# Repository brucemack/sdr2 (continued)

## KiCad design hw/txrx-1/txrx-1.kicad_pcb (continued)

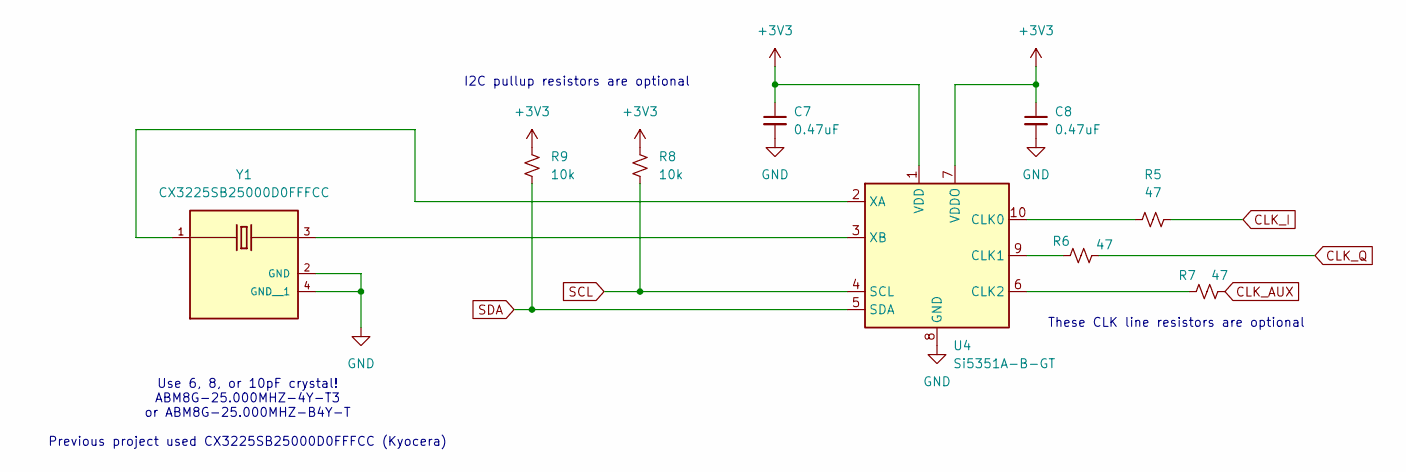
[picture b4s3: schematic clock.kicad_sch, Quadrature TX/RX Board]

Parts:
C7, C8: 0.47uF; C_0805_2012Metric_Pad1.18x1.45mm_HandSolder
R5, R6, R7: 47; R_0805_2012Metric_Pad1.20x1.40mm_HandSolder
R8, R9: 10k; R_0805_2012Metric_Pad1.20x1.40mm_HandSolder
U4: Si5351A-B-GT; MSOP-10_3x3mm_P0.5mm
Y1: CX3225SB25000D0FFFCC; OSCCC320X250X60N; PARTREV N/A

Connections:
+3V3: C7.1, C8.1, R8.1, R9.1, U4.1 (VDD), U4.7 (VDDO); also elsewhere on the board
CLK_AUX: R7.2; also elsewhere on the board
CLK_I: R5.2; also elsewhere on the board
CLK_Q: R6.2; also elsewhere on the board
GND: C7.2, C8.2, U4.8 (GND), Y1.2 (GND), Y1.4 (GND__1); also elsewhere on the board
unnamed: R5.1, U4.10 (CLK0)
unnamed: R6.1, U4.9 (CLK1)
unnamed: R7.1, U4.6 (CLK2)
unnamed: U4.2 (XA), Y1.1
unnamed: U4.3 (XB), Y1.3
SCL: R8.2, U4.4 (SCL); also elsewhere on the board
SDA: R9.2, U4.5 (SDA); also elsewhere on the board

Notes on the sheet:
These CLK line resistors are optional
I2C pullup resistors are optional
Use 6, 8, or 10pF crystal! ABM8G-25.000MHZ-4Y-T3 or ABM8G-25.000MHZ-B4Y-T Previous project used CX3225SB25000D0FFFCC (Kyocera)

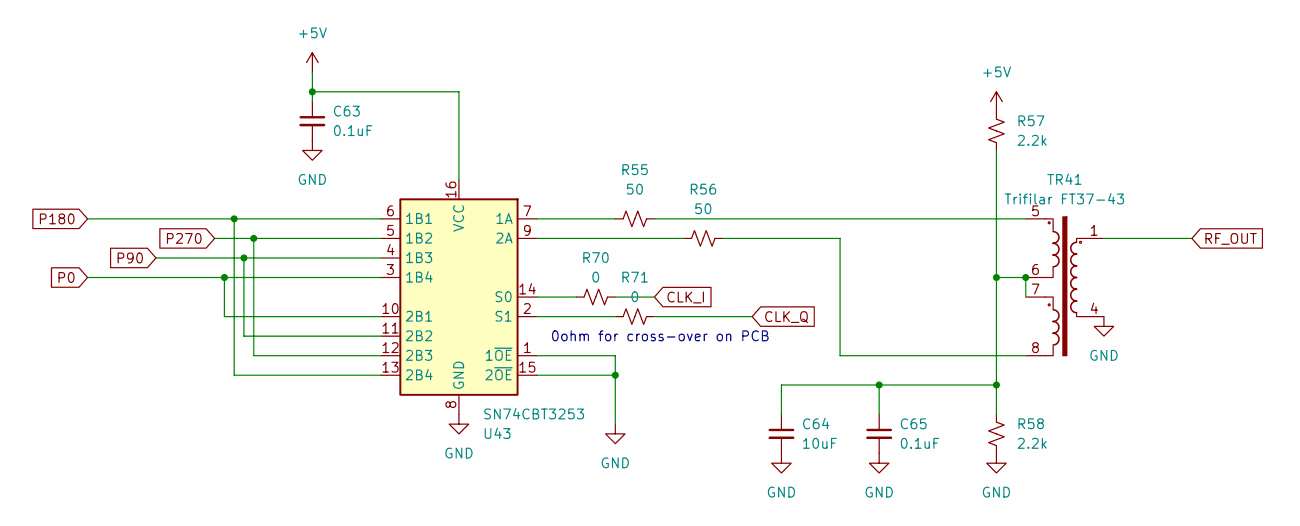
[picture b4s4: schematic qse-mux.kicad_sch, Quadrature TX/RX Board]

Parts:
C63, C65: 0.1uF; C_0805_2012Metric_Pad1.18x1.45mm_HandSolder
C64: 10uF; C_0805_2012Metric_Pad1.18x1.45mm_HandSolder
R55, R56: 50; R_0805_2012Metric_Pad1.20x1.40mm_HandSolder
R57, R58: 2.2k; R_0805_2012Metric_Pad1.20x1.40mm_HandSolder
R70, R71: 0; R_0805_2012Metric_Pad1.20x1.40mm_HandSolder
TR41: Trifilar FT37-43; FT37-43 Trifilar
U43: SN74CBT3253; SOIC-16_3.9x9.9mm_P1.27mm

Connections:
+5V: C63.1, R57.1, U43.16 (VCC); also elsewhere on the board
CLK_I: R70.2; also elsewhere on the board
CLK_Q: R71.2; also elsewhere on the board
GND: C63.2, C64.2, C65.2, R58.2, TR41.4, U43.1 (1~OE), U43.8 (GND), U43.15 (2~OE); also elsewhere on the board
unnamed: C64.1, C65.1, R57.2, R58.1, TR41.6, TR41.7
unnamed: R55.2, TR41.5
unnamed: R56.2, TR41.8
unnamed: R55.1, U43.7 (1A)
unnamed: R56.1, U43.9 (2A)
unnamed: R70.1, U43.14 (S0)
unnamed: R71.1, U43.2 (S1)
P0: U43.3 (1B4), U43.10 (2B1); also elsewhere on the board
P90: U43.4 (1B3), U43.11 (2B2); also elsewhere on the board
P180: U43.6 (1B1), U43.13 (2B4); also elsewhere on the board
P270: U43.5 (1B2), U43.12 (2B3); also elsewhere on the board
RF_OUT: TR41.1; also elsewhere on the board

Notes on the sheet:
0ohm for cross-over on PCB

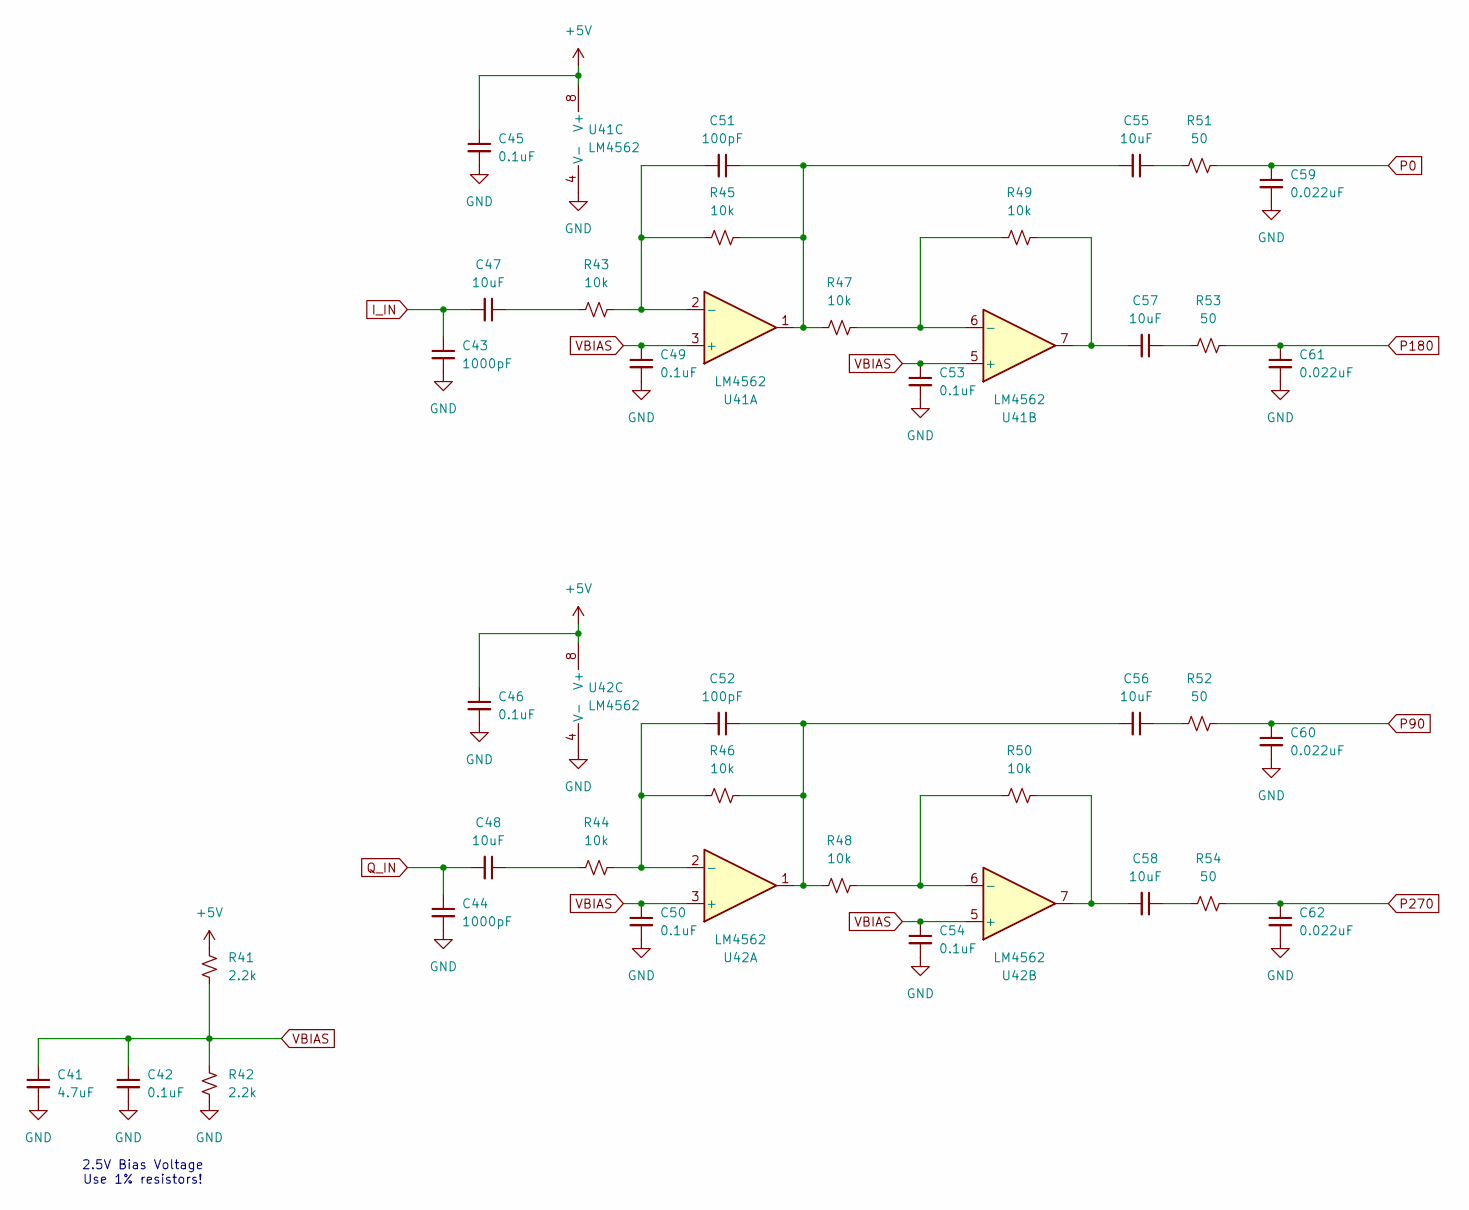
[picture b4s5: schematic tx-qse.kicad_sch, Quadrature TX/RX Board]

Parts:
C41: 4.7uF; C_0805_2012Metric_Pad1.18x1.45mm_HandSolder
C42, C45, C46, C49, C50, C53, C54: 0.1uF; C_0805_2012Metric_Pad1.18x1.45mm_HandSolder
C43, C44: 1000pF; C_0805_2012Metric_Pad1.18x1.45mm_HandSolder
C47, C48, C55, C56, C57, C58: 10uF; C_0805_2012Metric_Pad1.18x1.45mm_HandSolder
C51, C52: 100pF; C_0805_2012Metric_Pad1.18x1.45mm_HandSolder
C59, C60, C61, C62: 0.022uF; C_0805_2012Metric_Pad1.18x1.45mm_HandSolder
R41, R42: 2.2k; R_0805_2012Metric_Pad1.20x1.40mm_HandSolder
R43, R44, R45, R46, R47, R48, R49, R50: 10k; R_0805_2012Metric_Pad1.20x1.40mm_HandSolder
R51, R52, R53, R54: 50; R_0805_2012Metric_Pad1.20x1.40mm_HandSolder
U41, U42: LM4562; SOIC-8_3.9x4.9mm_P1.27mm

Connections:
+5V: C45.1, C46.1, R41.1, U41.8 (V+), U42.8 (V+); also elsewhere on the board
GND: C41.2, C42.2, C43.2, C44.2, C45.2, C46.2, C49.2, C50.2, C53.2, C54.2, C59.2, C60.2, C61.2, C62.2, R42.2, U41.4 (V-), U42.4 (V-); also elsewhere on the board
I_IN: C43.1, C47.2; also elsewhere on the board
unnamed: C47.1, R43.1
unnamed: C48.1, R44.1
unnamed: C51.1, C55.2, R45.2, R47.1, U41.1
unnamed: C52.1, C56.2, R46.2, R48.1, U42.1
unnamed: C55.1, R51.1
unnamed: C56.1, R52.1
unnamed: C57.1, R53.1
unnamed: C57.2, R49.2, U41.7
unnamed: C58.1, R54.1
unnamed: C58.2, R50.2, U42.7
unnamed: C51.2, R43.2, R45.1, U41.2 (-)
unnamed: R47.2, R49.1, U41.6 (-)
unnamed: C52.2, R44.2, R46.1, U42.2 (-)
unnamed: R48.2, R50.1, U42.6 (-)
P0: C59.1, R51.2; also elsewhere on the board
P90: C60.1, R52.2; also elsewhere on the board
P180: C61.1, R53.2; also elsewhere on the board
P270: C62.1, R54.2; also elsewhere on the board
Q_IN: C44.1, C48.2; also elsewhere on the board
VBIAS: C41.1, C42.1, C49.1, C50.1, C53.1, C54.1, R41.2, R42.1, U41.3 (+), U41.5 (+), U42.3 (+), U42.5 (+)

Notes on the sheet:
2.5V Bias Voltage Use 1% resistors!

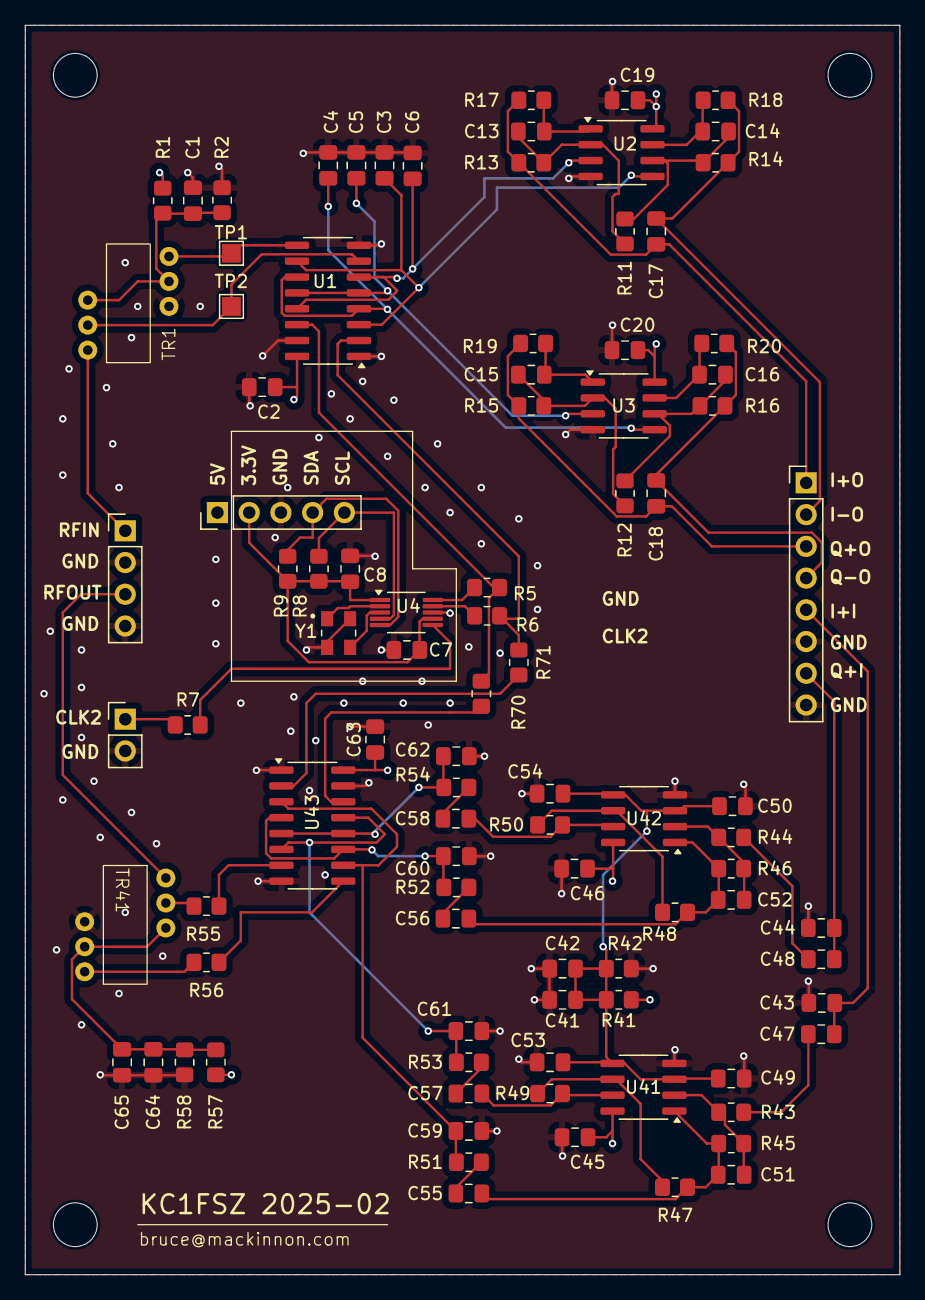
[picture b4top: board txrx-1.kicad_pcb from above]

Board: 4 copper layers, 70.0 x 100.0 mm, 98 parts (0 on the bottom side), 62 nets.

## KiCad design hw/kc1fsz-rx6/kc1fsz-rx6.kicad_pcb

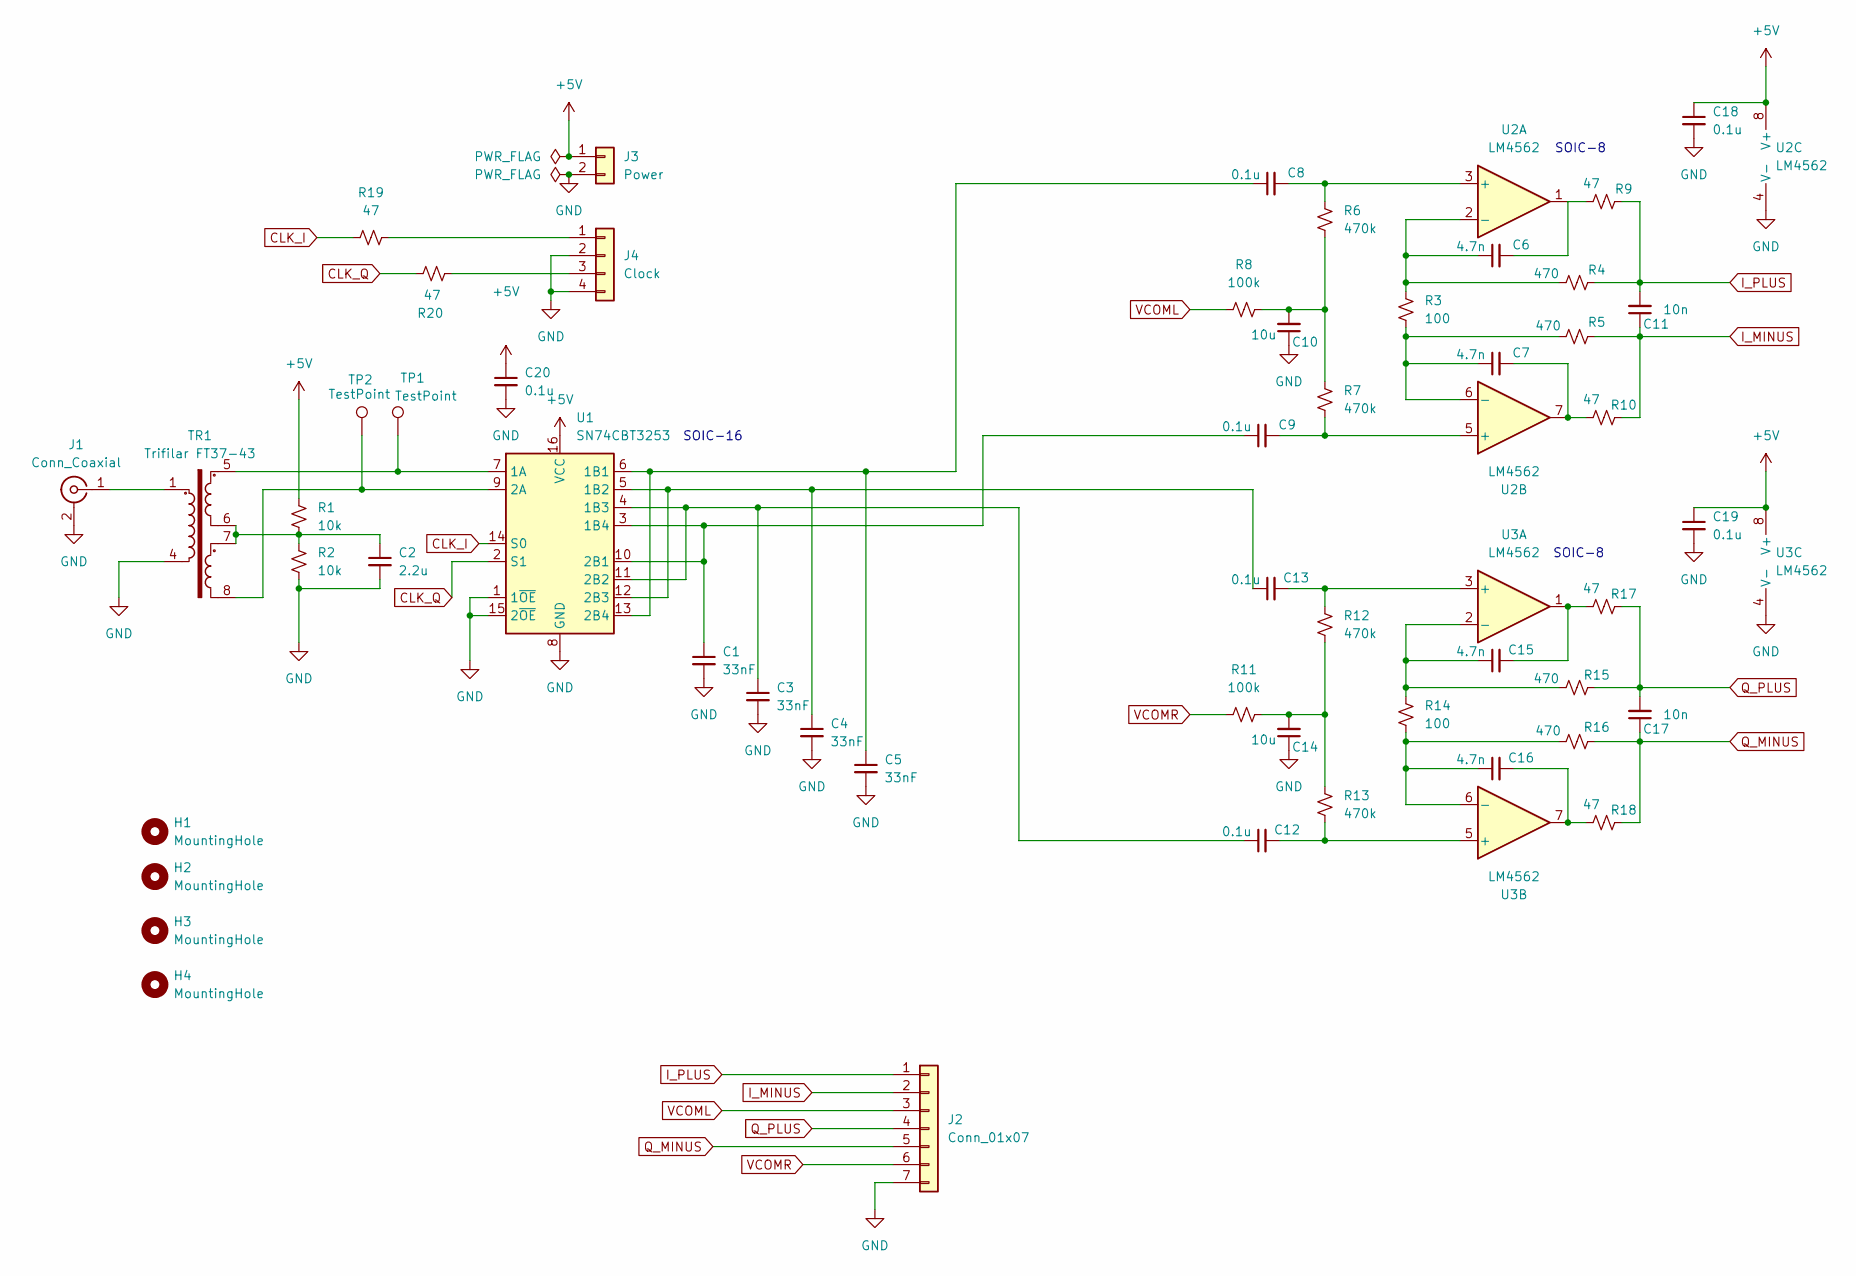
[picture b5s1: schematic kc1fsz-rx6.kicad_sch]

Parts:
C1, C3, C4, C5: 33nF; C_0805_2012Metric_Pad1.18x1.45mm_HandSolder
C2: 2.2u; C_0805_2012Metric_Pad1.18x1.45mm_HandSolder
C6, C7, C15, C16: 4.7n; C_0805_2012Metric_Pad1.18x1.45mm_HandSolder
C8, C9, C12, C13, C18, C19, C20: 0.1u; C_0805_2012Metric_Pad1.18x1.45mm_HandSolder
C10, C14: 10u; C_0805_2012Metric_Pad1.18x1.45mm_HandSolder
C11, C17: 10n; C_0805_2012Metric_Pad1.18x1.45mm_HandSolder
H1, H2, H3, H4: MountingHole; MountingHole_3.5mm
J1: Conn_Coaxial; SMA_Amphenol_901-144_Vertical
J2: Conn_01x07; PinHeader_1x07_P2.54mm_Vertical
J3: Power; PinHeader_1x02_P2.54mm_Vertical
J4: Clock; PinHeader_1x04_P2.54mm_Vertical
R1, R2: 10k; R_0805_2012Metric_Pad1.20x1.40mm_HandSolder
R3, R14: 100; R_0805_2012Metric_Pad1.20x1.40mm_HandSolder
R4, R5, R15, R16: 470; R_0805_2012Metric_Pad1.20x1.40mm_HandSolder
R6, R7, R12, R13: 470k; R_0805_2012Metric_Pad1.20x1.40mm_HandSolder
R8, R11: 100k; R_0805_2012Metric_Pad1.20x1.40mm_HandSolder
R9, R10, R17, R18, R19, R20: 47; R_0805_2012Metric_Pad1.20x1.40mm_HandSolder
TP1, TP2: TestPoint; TestPoint_Pad_1.5x1.5mm
TR1: Trifilar FT37-43; FT37-43 Trifilar
U1: SN74CBT3253; SOIC-16_3.9x9.9mm_P1.27mm
U2, U3: LM4562; SOIC-8_3.9x4.9mm_P1.27mm

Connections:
+5V: C18.1, C19.1, C20.1, J3.1, R1.1, U1.16 (VCC), U2.8 (V+), U3.8 (V+)
CLK_I: R19.1, U1.14 (S0)
CLK_Q: R20.1, U1.2 (S1)
GND: C1.2, C2.2, C3.2, C4.2, C5.2, C10.1, C14.1, C18.2, C19.2, C20.2, J1.2 (Ext), J2.7, J3.2, J4.2, J4.4, R2.2, TR1.4, U1.1 (1~OE), U1.8 (GND), U1.15 (2~OE), U2.4 (V-), U3.4 (V-)
I_MINUS: C11.1, J2.2, R5.2, R10.2
I_PLUS: C11.2, J2.1, R4.2, R9.2
unnamed: C2.1, R1.2, R2.1, TR1.6, TR1.7
unnamed: C6.2, R9.1, U2.1
unnamed: C7.2, R10.1, U2.7
unnamed: C10.2, R6.2, R7.1, R8.2
unnamed: C14.2, R11.2, R12.2, R13.1
unnamed: C15.2, R17.1, U3.1
unnamed: C16.2, R18.1, U3.7
unnamed: J1.1 (In), TR1.1
unnamed: J4.1, R19.2
unnamed: J4.3, R20.2
unnamed: TP1.1, TR1.5, U1.7 (1A)
unnamed: C5.1, C8.1, U1.6 (1B1), U1.13 (2B4)
unnamed: C4.1, C13.1, U1.5 (1B2), U1.12 (2B3)
unnamed: C3.1, C12.1, U1.4 (1B3), U1.11 (2B2)
unnamed: C1.1, C9.1, U1.3 (1B4), U1.10 (2B1)
unnamed: TP2.1, TR1.8, U1.9 (2A)
unnamed: C8.2, R6.1, U2.3 (+)
unnamed: C6.1, R3.1, R4.1, U2.2 (-)
unnamed: C9.2, R7.2, U2.5 (+)
unnamed: C7.1, R3.2, R5.1, U2.6 (-)
unnamed: C13.2, R12.1, U3.3 (+)
unnamed: C15.1, R14.1, R15.1, U3.2 (-)
unnamed: C12.2, R13.2, U3.5 (+)
unnamed: C16.1, R14.2, R16.1, U3.6 (-)
Q_MINUS: C17.1, J2.5, R16.2, R18.2
Q_PLUS: C17.2, J2.4, R15.2, R17.2
VCOML: J2.3, R8.1
VCOMR: J2.6, R11.1

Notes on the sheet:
SOIC-8
SOIC-16

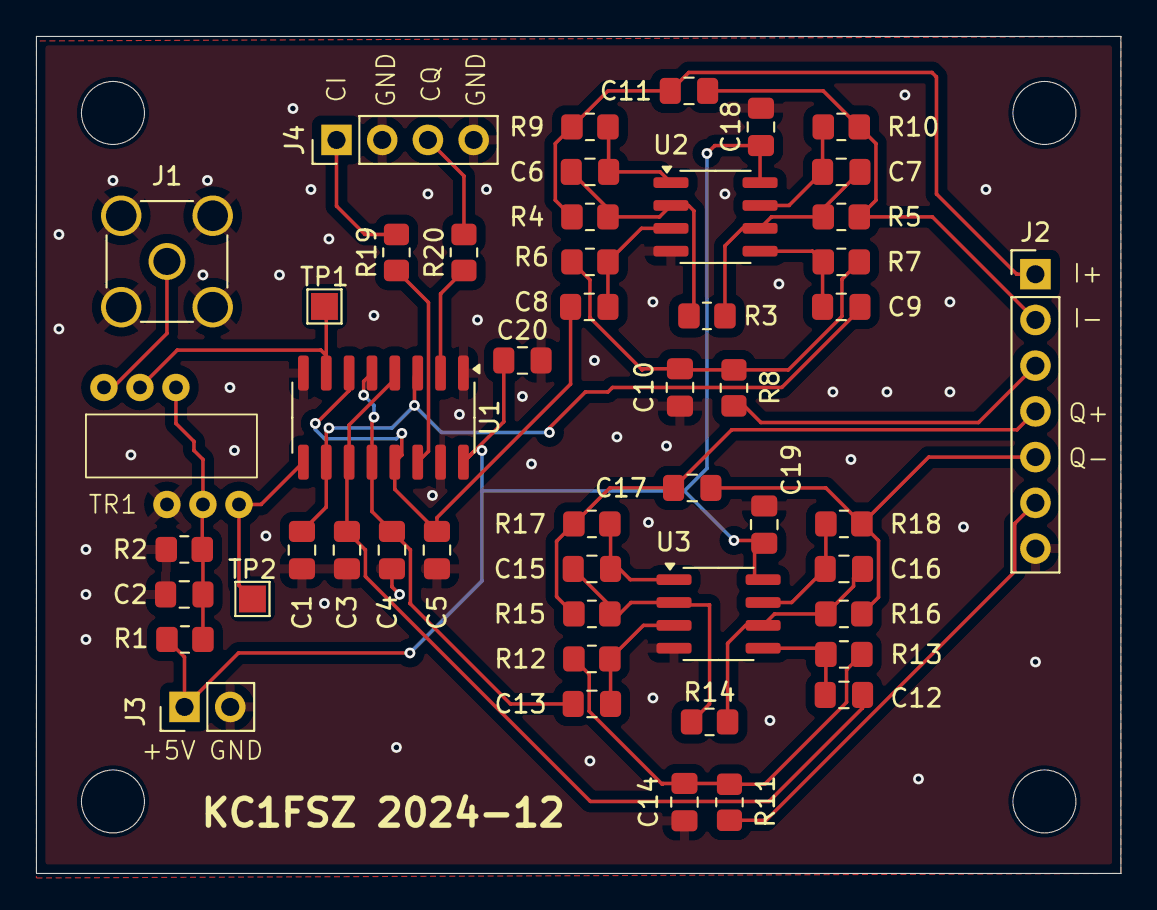
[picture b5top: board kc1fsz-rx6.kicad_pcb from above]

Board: 2 copper layers, 60.2 x 46.5 mm, 54 parts (0 on the bottom side), 34 nets.

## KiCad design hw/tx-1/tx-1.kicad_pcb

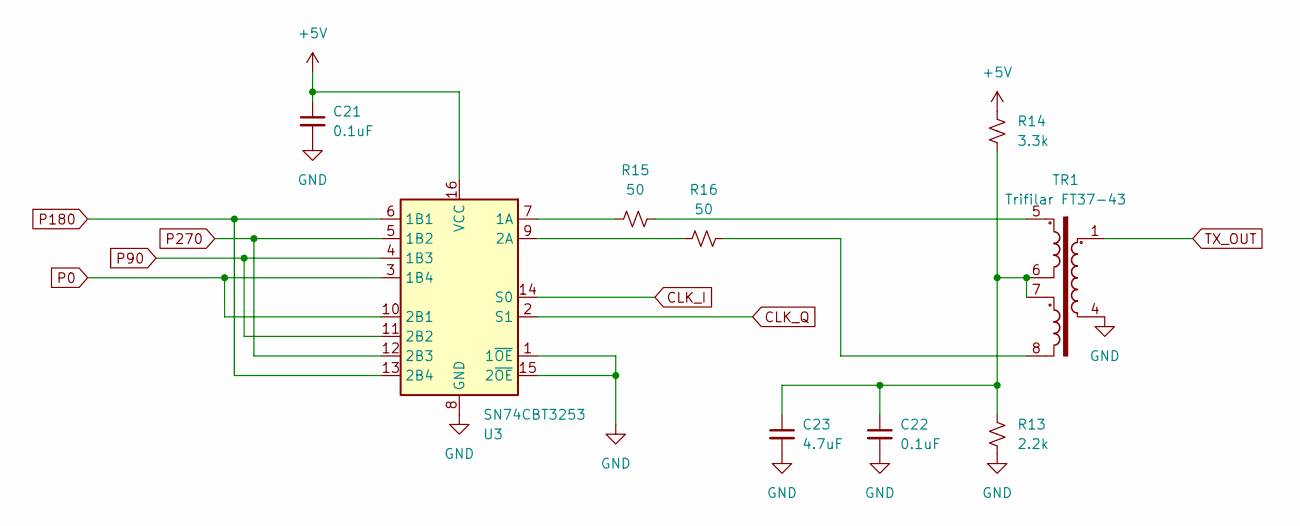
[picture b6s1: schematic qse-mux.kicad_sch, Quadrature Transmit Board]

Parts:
C21, C22: 0.1uF; C_0805_2012Metric_Pad1.18x1.45mm_HandSolder
C23: 4.7uF; C_0805_2012Metric_Pad1.18x1.45mm_HandSolder
R13: 2.2k; R_0805_2012Metric_Pad1.20x1.40mm_HandSolder
R14: 3.3k; R_0805_2012Metric_Pad1.20x1.40mm_HandSolder
R15, R16: 50; R_0805_2012Metric_Pad1.20x1.40mm_HandSolder
TR1: Trifilar FT37-43; FT37-43 Trifilar
U3: SN74CBT3253; SOIC-16_3.9x9.9mm_P1.27mm

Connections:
+5V: C21.1, R14.1, U3.16 (VCC); also elsewhere on the board
CLK_I: U3.14 (S0); also elsewhere on the board
CLK_Q: U3.2 (S1); also elsewhere on the board
GND: C21.2, C22.2, C23.2, R13.2, TR1.4, U3.1 (1~OE), U3.8 (GND), U3.15 (2~OE); also elsewhere on the board
unnamed: C22.1, C23.1, R13.1, R14.2, TR1.6, TR1.7
unnamed: R15.2, TR1.5
unnamed: R16.2, TR1.8
unnamed: R15.1, U3.7 (1A)
unnamed: R16.1, U3.9 (2A)
P0: U3.3 (1B4), U3.10 (2B1); also elsewhere on the board
P90: U3.4 (1B3), U3.11 (2B2); also elsewhere on the board
P180: U3.6 (1B1), U3.13 (2B4); also elsewhere on the board
P270: U3.5 (1B2), U3.12 (2B3); also elsewhere on the board
TX_OUT: TR1.1; also elsewhere on the board

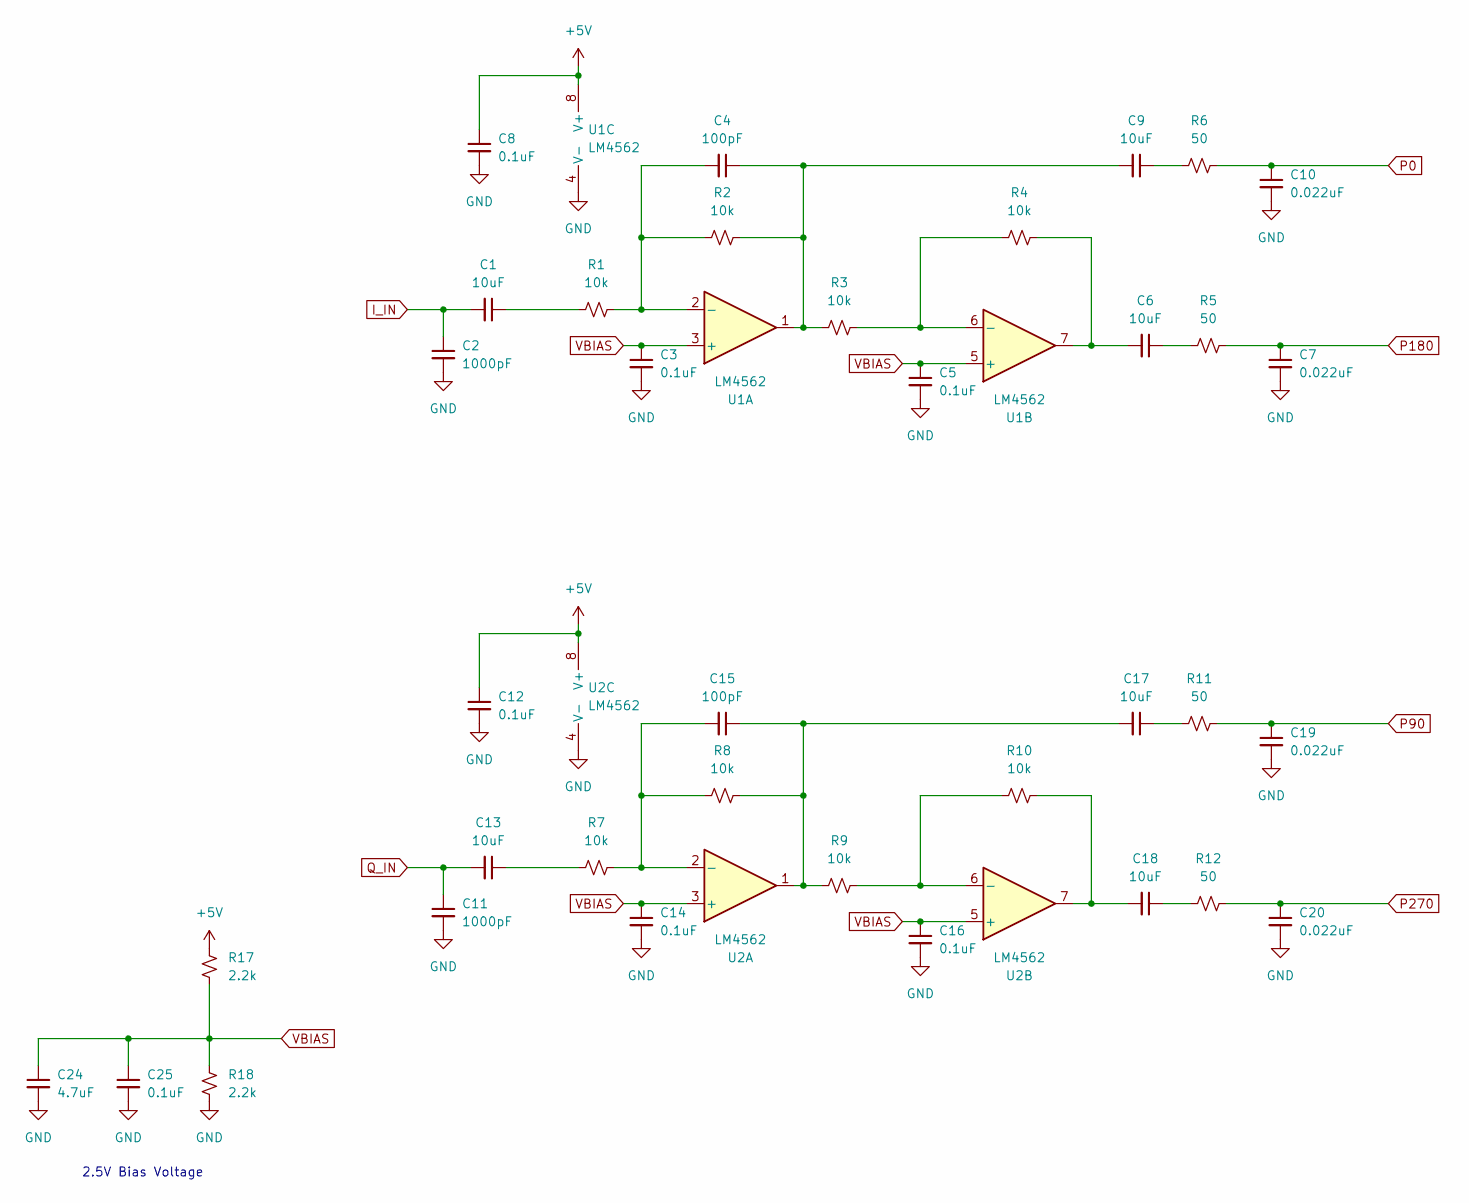
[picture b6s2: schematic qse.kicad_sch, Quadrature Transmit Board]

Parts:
C1, C6, C9, C13, C17, C18: 10uF; C_0805_2012Metric_Pad1.18x1.45mm_HandSolder
C2, C11: 1000pF; C_0805_2012Metric_Pad1.18x1.45mm_HandSolder
C3, C5, C8, C12, C14, C16, C25: 0.1uF; C_0805_2012Metric_Pad1.18x1.45mm_HandSolder
C4, C15: 100pF; C_0805_2012Metric_Pad1.18x1.45mm_HandSolder
C7, C10, C19, C20: 0.022uF; C_0805_2012Metric_Pad1.18x1.45mm_HandSolder
C24: 4.7uF; C_0805_2012Metric_Pad1.18x1.45mm_HandSolder
R1, R2, R3, R4, R7, R8, R9, R10: 10k; R_0805_2012Metric_Pad1.20x1.40mm_HandSolder
R5, R6, R11, R12: 50; R_0805_2012Metric_Pad1.20x1.40mm_HandSolder
R17, R18: 2.2k; R_0805_2012Metric_Pad1.20x1.40mm_HandSolder
U1, U2: LM4562; SOIC-8_3.9x4.9mm_P1.27mm

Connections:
+5V: C8.1, C12.1, R17.1, U1.8 (V+), U2.8 (V+); also elsewhere on the board
GND: C2.2, C3.2, C5.2, C7.2, C8.2, C10.2, C11.2, C12.2, C14.2, C16.2, C19.2, C20.2, C24.2, C25.2, R18.2, U1.4 (V-), U2.4 (V-); also elsewhere on the board
I_IN: C1.2, C2.1; also elsewhere on the board
unnamed: C1.1, R1.1
unnamed: C4.1, C9.2, R2.2, R3.1, U1.1
unnamed: C6.1, R5.1
unnamed: C6.2, R4.2, U1.7
unnamed: C9.1, R6.1
unnamed: C13.1, R7.1
unnamed: C15.1, C17.2, R8.2, R9.1, U2.1
unnamed: C17.1, R11.1
unnamed: C18.1, R12.1
unnamed: C18.2, R10.2, U2.7
unnamed: C4.2, R1.2, R2.1, U1.2 (-)
unnamed: R3.2, R4.1, U1.6 (-)
unnamed: C15.2, R7.2, R8.1, U2.2 (-)
unnamed: R9.2, R10.1, U2.6 (-)
P0: C10.1, R6.2; also elsewhere on the board
P90: C19.1, R11.2; also elsewhere on the board
P180: C7.1, R5.2; also elsewhere on the board
P270: C20.1, R12.2; also elsewhere on the board
Q_IN: C11.1, C13.2; also elsewhere on the board
VBIAS: C3.1, C5.1, C14.1, C16.1, C24.1, C25.1, R17.2, R18.1, U1.3 (+), U1.5 (+), U2.3 (+), U2.5 (+)

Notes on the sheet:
2.5V Bias Voltage

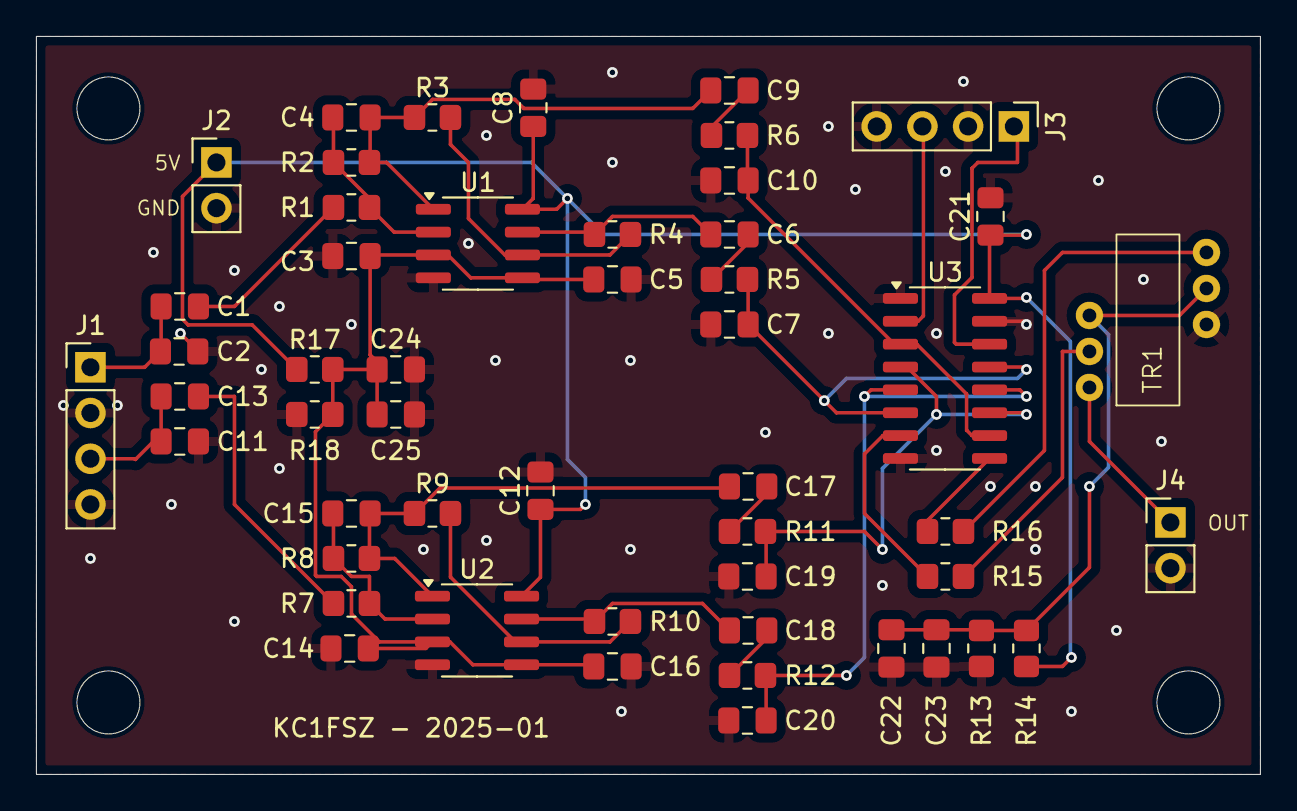
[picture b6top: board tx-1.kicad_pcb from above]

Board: 2 copper layers, 68.0 x 41.0 mm, 55 parts (0 on the bottom side), 31 nets.

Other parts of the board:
H1, H2, H3, H4: MountingHole; MountingHole_3.5mm
J1, J3: Conn_01x04; PinHeader_1x04_P2.54mm_Vertical
J2, J4: Conn_01x02; PinHeader_1x02_P2.54mm_Vertical

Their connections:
+5V: J2.1; also elsewhere on the board
CLK_I: J3.1; also elsewhere on the board
CLK_Q: J3.3; also elsewhere on the board
GND: J1.2, J1.4, J2.2, J3.2, J3.4, J4.2; also elsewhere on the board
I_IN: J1.1; also elsewhere on the board
Q_IN: J1.3; also elsewhere on the board
TX_OUT: J4.1; also elsewhere on the board

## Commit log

2025-01-20 SSB rejection seems to be working
2025-01-21 Working well
2025-01-24 Adding DAC
2025-01-24 First successful audio demo
2025-01-24 Added overflow detector
2025-01-25 Added sweep
2025-01-26 Working on tests
2025-01-26 Moving in hardware projects
2025-01-27 Ready to send audio breakout to fab
2025-01-28 TX board
2025-01-28 Working on TX
2025-01-29 Layout of TX board complete
2025-01-29 Ready to sent to fab
2025-02-04 Master generation of BCK and LRCK working
2025-02-05 Still debugging slave mode
2025-02-05 Slave mode problem resoled, now having a timing issue
2025-02-05 System working with PCM1804 in slave mode
2025-02-09 DAC working with DMA finally!
2025-02-10 Switched over to SMSIS DSP functions - not tested yet.
2025-02-11 Getting very close to working. Still a problem with pure tones
2025-02-11 RX working well
2025-02-12 TX test successful
2025-02-12 Initial TX test has passed
2025-02-12 Working on delay
2025-02-12 Making phase and imbalance user-adjustable
2025-02-12 Adding pictures
2025-02-12 Docs
2025-02-13 New board for power, etc
2025-02-13 Initial version of PCB layout
2025-02-14 Added changes to mic preamp ground plane
2025-02-14 Sending to OSHPark
2025-02-16 Working on converged TX/RX board
2025-02-17 Initial PCB layout for TXRX board
2025-02-17 Final version being sent to fab
2025-02-18 Sending revision of util-1 to JLCPCB
2025-02-24 First commit of BPF-1
2025-02-24 Ready to send to fab
2025-02-28 Working on new boards
2025-02-28 Working
2025-02-28 Working on gain calcs
2025-03-02 Refacting with new board
